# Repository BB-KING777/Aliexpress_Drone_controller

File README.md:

# Aliexpress_Drone_controller

# MINE VESPER - Custom Drone Controller

中国製激安ドローン（GT3）の通信プロトコルをリバースエンジニアリングし、ESP32ベースのカスタムコントローラーを開発したプロジェクトです。

## 📖 概要

このプロジェクトは、Aliexpressで約3000円で販売されている2.4GHz帯ドローンの通信プロトコルを解析し、専用のハードウェアコントローラーを自作したものです。約3ヶ月にわたる試行錯誤の末、WiFi（802.11）上のUDP通信で123バイトのパケットを送信する独自プロトコルを解明しました。

### 主な特徴

- **完全なプロトコル実装**: リバースエンジニアリングにより解明した123バイトパケットを完全再現
- **リアルタイム制御**: 80Hz（約13ms間隔）での高速パケット送信
- **直感的な操作**: ALPS製2軸アナログジョイスティックによる滑らかな制御
- **視認性の高いUI**: SSD1306 OLEDディスプレイでリアルタイム表示
- **低コスト**: 総製作コスト約2000円（基板製造費込み）

## 🎥 デモ

詳細な解析プロセスとデモ動画は、[ブログ記事](https://qurest.vercel.app/blog/2025-09-21-2-4Ghz-hacking)をご覧ください。

## 🛠️ ハードウェア

### 必要な部品

| 部品 | 型番/仕様 | 数量 | 参考価格 |
|------|-----------|------|----------|
| マイコンモジュール | ESP32-WROOM-32D | 1 | 約1,500円 |
| アナログジョイスティック | ALPS RKJXV1224005 | 1 | 約800円 |
| OLEDディスプレイ | SSD1306 (128×64, I2C) | 1 | 約500円 |
| タクトスイッチ | 6mm 4ピン | 5 | 約50円 |
| 抵抗 | 10kΩ | 4 | 約20円 |
| PCB | - | 1 | 約500円 |

**合計**: 約2,000円（基板製造費込み）

### 基板設計

PCB設計ファイルは`/hardware`ディレクトリに格納されています。

- **設計ツール**: KiCad
- **基板サイズ**: コンパクト設計（ポケットサイズ）
- **実装方式**: スルーホール実装（はんだ付け難易度: 低）
- **推奨製造業者**: JLCPCB, PCBWay, Elecrow など

## 💻 ファームウェア

### 環境構築

1. **Arduino IDEのインストール**
   - [Arduino IDE](https://www.arduino.cc/en/software)をダウンロード
   - ESP32ボードマネージャーをインストール
     - ファイル → 環境設定 → 追加のボードマネージャのURL:
```
     https://raw.githubusercontent.com/espressif/arduino-esp32/gh-pages/package_esp32_index.json
```

2. **必要なライブラリのインストール**
   - Adafruit GFX Library
   - Adafruit SSD1306
   - WiFi (ESP32標準)
   - WiFiUdp (ESP32標準)

### ファームウェアの書き込み

1. リポジトリをクローン
```bash
   git clone https://github.com/yourusername/MINE-VESPER.git
   cd MINE-VESPER
```

2. Arduino IDEで`firmware/MINE_VESPER.ino`を開く

3. ボード設定
   - ボード: "ESP32 Dev Module"
   - Upload Speed: "115200"
   - Flash Frequency: "80MHz"

4. シリアルポートを選択して書き込み

### 主な機能

- **WiFiスキャン**: 起動時に周辺のアクセスポイントを自動スキャン
- **AP接続**: ボタン操作でドローンのAPを選択・接続
- **制御モード**: 
  - ロール/ピッチ/スロットル/ヨーの連続制御
  - 離陸/着陸コマンド
  - ジャイロキャリブレーション
  - ヘッドレスモード切替
- **リアルタイム表示**: 制御値、ADC値、接続状態を表示

### カスタマイズ可能なパラメータ

`firmware/MINE_VESPER.ino`内で以下のパラメータを調整できます。
```cpp
// ジョイスティックの感度
#define JOYSTICK_EMA_ALPHA 1.0        // 1.0 = ピーキー, 0.3 = スムーズ

// 制御の平滑化
#define CONTROL_SMOOTH_ALPHA 1.0      // 1.0 = 即応性高, 0.5 = 安定性高

// デッドゾーン
#define STICK_DEADZONE 100            // 中央付近の不感帯

// Expoカーブ
#define STICK_EXPO 0.0                // 0.0 = リニア, 0.5 = 中央付近が敏感

// 送信レート
#define CONTROL_INTERVAL 13           // ms (約80Hz)
```

## 📡 通信プロトコル

### 概要

- **プロトコル**: UDP over WiFi (802.11)
- **ポート番号**: 8800
- **IPアドレス**: 192.168.169.1（ドローン固定IP）
- **送信方式**: Fire-and-Forget（一方向送信）
- **送信レート**: 80Hz（約13ms間隔）

### パケット構造（123バイト）

パケットは6つのブロックで構成されています。
```
[ヘッダー 12B] [カウンター1 8B] [制御データ 16B] [チェックサム 51B] [カウンター2 20B] [カウンター3 16B]
```

#### ブロック3: 制御データ（最重要）

| オフセット | 名前 | 範囲 | 説明 |
|-----------|------|------|------|
| 0 | Roll | 40-220 | ロール（左右傾き）、中央値: 128 |
| 1 | Pitch | 40-220 | ピッチ（前後傾き）、中央値: 128 |
| 2 | Throttle | 40-220 | スロットル（上昇/下降）、中央値: 128 |
| 3 | Yaw | 40-220 | ヨー（回転）、中央値: 128 |
| 4 | Command | 0x00-0x04 | コマンドバイト（下表参照） |
| 5 | Headless | 0x02/0x03 | ヘッドレスモード (OFF: 0x02, ON: 0x03) |

#### コマンド一覧

| 値 | コマンド | 説明 |
|----|----------|------|
| 0x00 | NEUTRAL | 待機状態（常時送信） |
| 0x01 | TAKEOFF | 離陸 |
| 0x02 | LAND | 着陸/緊急停止 |
| 0x04 | CALIBRATE | ジャイロキャリブレーション |

詳細なパケット構造は[プロトコルドキュメント](docs/protocol.md)を参照してください。

## 🔧 組み立て手順

1. **PCB発注**
   - `/hardware/gerber`をZIP圧縮してJLCPCBなどに発注
   - 推奨オプション: 紫色、1.6mm厚

2. **部品実装**
   - スルーホール部品を順番にはんだ付け
   - **重要**: SSD1306の裏面に帯電防止テープを貼る

3. **ファームウェア書き込み**
   - ESP32にUSB接続してファームウェアを書き込み

4. **動作確認**
   - 電源投入 → WiFiスキャン → ドローンAP接続 → 制御テスト

詳細な組み立てガイドは[こちら](docs/assembly.md)。

## 📝 使い方

1. **起動**
   - コントローラーに電源を投入
   - 自動的にWiFiスキャンが開始されます

2. **接続**
   - 上下ボタンでドローンのAPを選択
   - 決定ボタン（中央）で接続

3. **操縦**
   - 左スティック: スロットル（上下）、ヨー（左右）
   - 右スティック: ピッチ（上下）、ロール（左右）
   - 上ボタン: 離陸
   - 下ボタン: 着陸
   - 左ボタン: ヘッドレスモード切替
   - 中央ボタン: ジャイロキャリブレーション

## 🚀 今後の拡張案

- [ ] リチウムバッテリー内蔵でポータブル化
- [ ] 録画機能の実装
- [ ] FPV（First Person View）対応
- [ ] 3Dプリントケースの設計
- [ ] Bluetoothゲームパッド対応
- [ ] テレメトリーデータ受信機能

## ⚠️ 免責事項

- このプロジェクトは教育・研究目的です
- ドローンの飛行は各国の法規制に従ってください
- リバースエンジニアリングは個人使用の範囲で行ってください
- プロジェクトの使用により生じた損害について、作者は一切の責任を負いません
- 安全な場所でテストを行い、事故には十分注意してください

## 📄 ライセンス

このプロジェクトはMITライセンスの下で公開されています。詳細は[LICENSE](LICENSE)ファイルを参照してください。

## 🙏 謝辞

- [cifertech氏](https://cifertech.net/) - nRF24L01スキャナーのガイド
- [atomic14氏](https://github.com/atomic14/basic-esp32s3-dev-board) - ESP32-S3基板設計の参考
- Adafruit - 優れたライブラリ群
- KiCad - 素晴らしいEDAツール

## 📚 参考資料

- [詳細なブログ記事](https://qurest.vercel.app/blog/2025-09-21-2-4Ghz-hacking) - 解析プロセスの全記録
- [プロトコル仕様](docs/protocol.md) - 通信プロトコルの詳細
- [組み立てガイド](docs/assembly.md) - ステップバイステップガイド

## 🤝 コントリビューション

プルリクエストを歓迎します！大きな変更の場合は、まずissueを開いて変更内容を議論してください。

## 📧 コンタクト

質問や提案がある場合は、[Issue](https://github.com/yourusername/MINE-VESPER/issues)を開くか、[ブログ](https://qurest.vercel.app/)のコメント欄でお知らせください。

---

**MINE VESPER** - Made with ❤️ by Waka

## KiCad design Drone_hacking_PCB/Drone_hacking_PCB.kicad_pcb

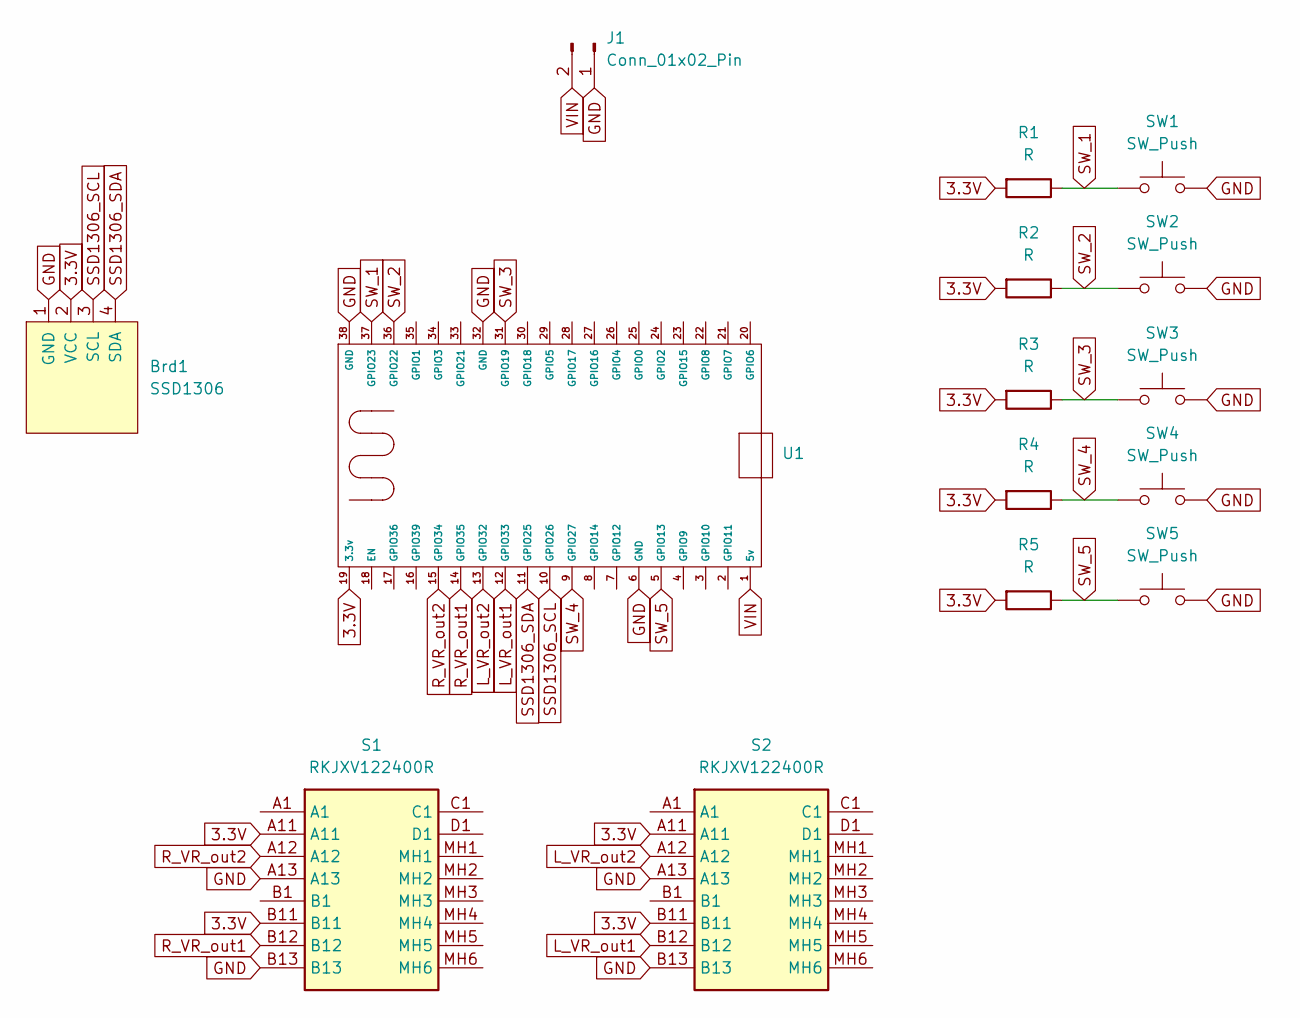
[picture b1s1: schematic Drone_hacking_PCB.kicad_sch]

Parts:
Brd1: SSD1306; 128x64OLED
J1: Conn_01x02_Pin; 4xAA battery
R1, R2, R3, R4, R5: R; R_Axial_DIN0207_L6.3mm_D2.5mm_P7.62mm_Horizontal
S1, S2: RKJXV122400R; Mouser Part Number 688-RKJXV122400R
SW1, SW2, SW3, SW4, SW5: SW_Push; SW_PUSH_6mm_H5mm
U1: ESP32_38pin

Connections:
3.3V: Brd1.2 (VCC), R1.2, R2.2, R3.2, R4.2, R5.2, S1.A11, S1.B11, S2.A11, S2.B11, U1.19 (3.3v)
GND: Brd1.1 (GND), J1.1, S1.A13, S1.B13, S2.A13, S2.B13, SW1.2, SW2.2, SW3.2, SW4.2, SW5.2, U1.6 (GND), U1.32 (GND), U1.38 (GND)
L_VR_out1: S2.B12, U1.12 (GPIO33)
L_VR_out2: S2.A12, U1.13 (GPIO32)
R_VR_out1: S1.B12, U1.14 (GPIO35)
R_VR_out2: S1.A12, U1.15 (GPIO34)
SSD1306_SCL: Brd1.3 (SCL), U1.10 (GPIO26)
SSD1306_SDA: Brd1.4 (SDA), U1.11 (GPIO25)
SW_1: R1.1, SW1.1, U1.37 (GPIO23)
SW_2: R2.1, SW2.1, U1.36 (GPIO22)
SW_3: R3.1, SW3.1, U1.31 (GPIO19)
SW_4: R4.1, SW4.1, U1.9 (GPIO27)
SW_5: R5.1, SW5.1, U1.5 (GPIO13)
VIN: J1.2, U1.1 (5v)

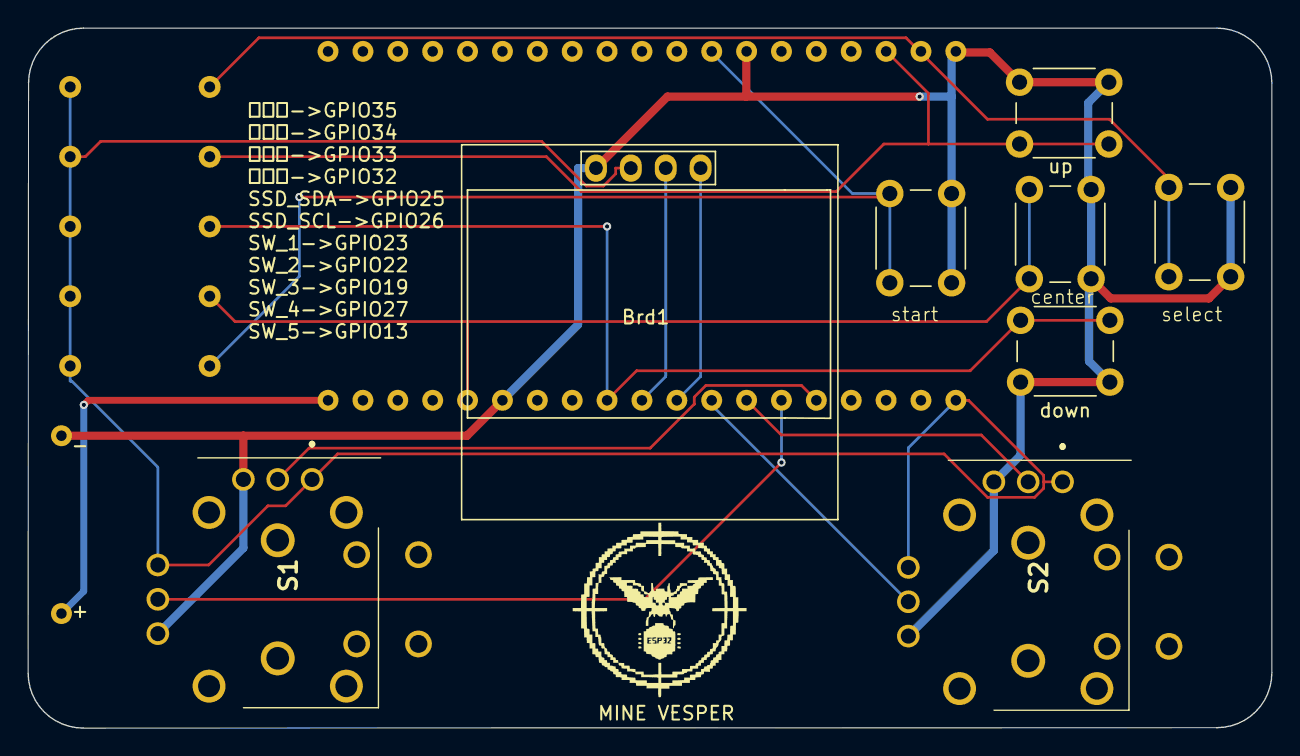
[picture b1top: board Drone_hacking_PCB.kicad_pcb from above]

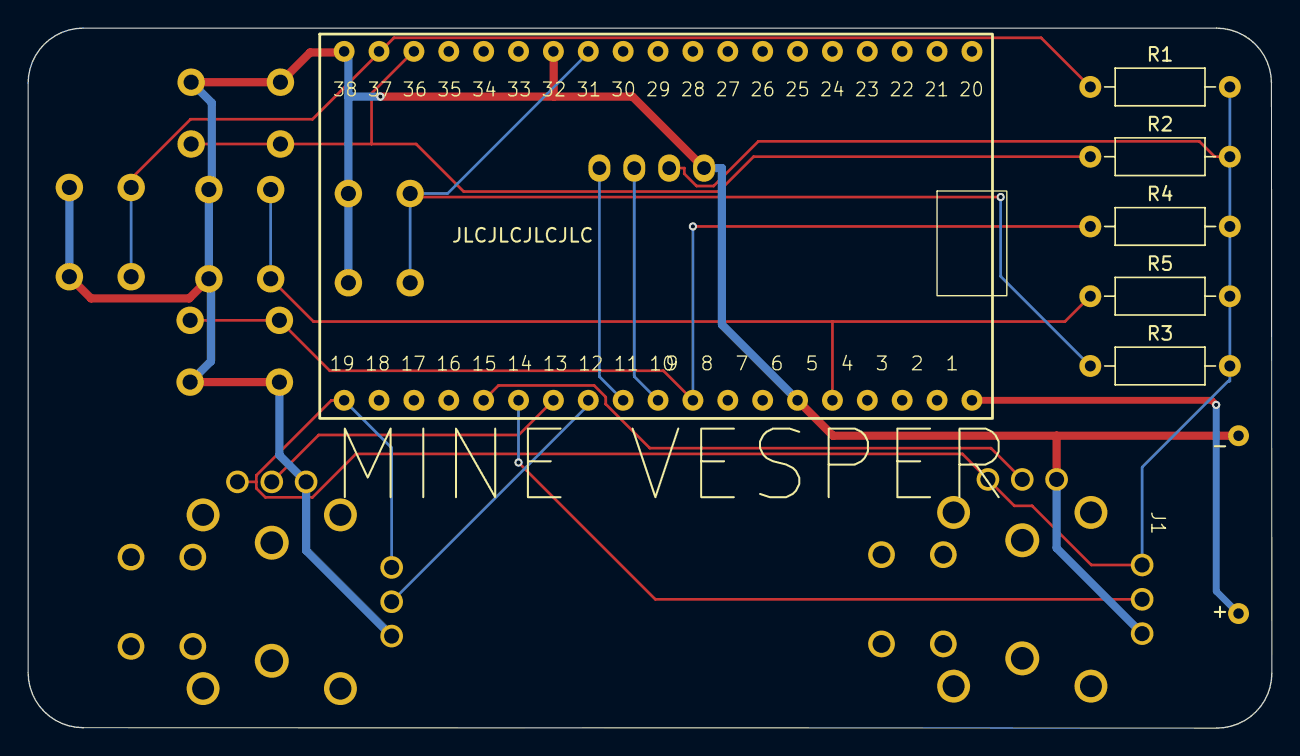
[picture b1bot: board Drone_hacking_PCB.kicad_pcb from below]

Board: 2 copper layers, 90.6 x 51.0 mm, 15 parts (7 on the bottom side), 14 nets.

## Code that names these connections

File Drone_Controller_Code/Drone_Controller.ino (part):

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Adafruit_SSD1306 display(SCREEN_WIDTH, SCREEN_HEIGHT, &Wire, OLED_RESET);

// --- ピン定義 (タクトスイッチ) ---
#define PIN_BTN_RIGHT 23 // SW_1 (未使用)
#define PIN_BTN_UP    22 // SW_2 (離陸)
#define PIN_BTN_LEFT  19 // SW_3 (Headless)
#define PIN_BTN_DOWN  27 // SW_4 (着陸)
#define PIN_BTN_OK    13 // SW_5 (キャリブレーション)

// --- ピン定義 (ジョイスティック) ---
#define PIN_LEFT_UD   35 // スロットル (Throttle)
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
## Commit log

2025-11-09 Enhance README with project details and instructions
    Added detailed project description, features, hardware requirements, firmware setup, communication protocol, assembly instructions, and contribution guidelines.

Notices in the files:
README.md:
License: MIT
